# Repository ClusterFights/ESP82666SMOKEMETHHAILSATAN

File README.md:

ESP82666SMOKEMETHHAILSATAN

Imps are like clients. They're small and should only consume work units
Devils are like hosts. They parse the datasets and create work units

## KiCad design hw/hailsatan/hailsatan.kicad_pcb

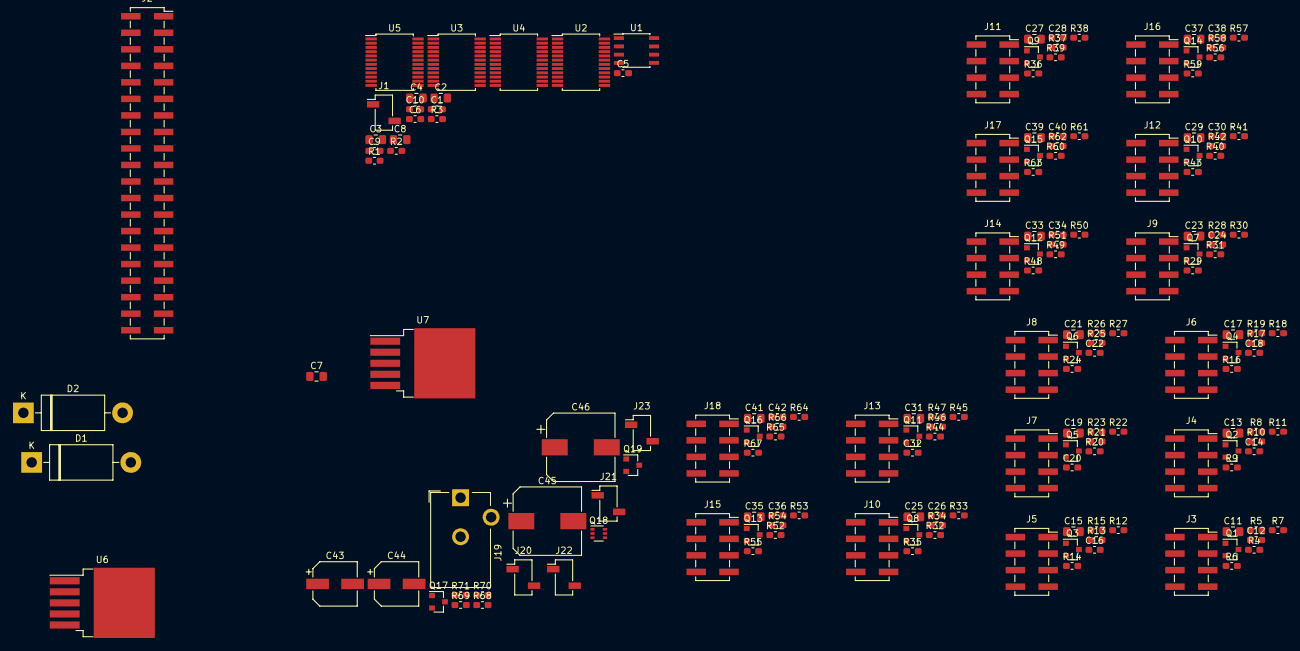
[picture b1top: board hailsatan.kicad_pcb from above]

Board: 2 copper layers, 168 parts (0 on the bottom side), 136 nets, no tracks yet.

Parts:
C1, C5, C6, C9, C10, C12, C14, C16, C18, C20, C22, C24, C26, C28, C30, C32, C34, C36, C38, C40, C42: 0.1uF; C_0603_1608Metric_Pad1.05x0.95mm_HandSolder
C2, C3, C4, C7, C8, C11, C13, C15, C17, C19, C21, C23, C25, C27, C29, C31, C33, C35, C37, C39, C41: 1uF; C_0805_2012Metric_Pad1.15x1.40mm_HandSolder
C43, C44: 100uF; CP_Elec_6.3x5.4_Nichicon
C45, C46: 1000uF; CP_Elec_10x10
D1, D2: 1N5822; D_DO-201AD_P15.24mm_Horizontal
J1, J20, J21, J22, J23: Conn_01x02; PinSocket_1x02_P2.54mm_Vertical_SMD_Pin1Left
J2: Raspberry_Pi_2_3; PinSocket_2x20_P2.54mm_Vertical_SMD
J3, J4, J5, J6, J7, J8, J9, J10, J11, J12, J13, J14, J15, J16, J17, J18: Conn_02x04_Odd_Even; PinSocket_2x04_P2.54mm_Vertical_SMD
J19: Barrel_Jack_Switch; BarrelJack_CUI_PJ-102AH_Horizontal
Q1, Q2, Q3, Q4, Q5, Q6, Q7, Q8, Q9, Q10, Q11, Q12, Q13, Q14, Q15, Q16, Q17: 2N7002; SOT-23
Q18: MMDT3906; SOT-363_SC-70-6
Q19: Si2319CDS; SOT-23
R1, R2, R3, R68, R69: 3.3k; R_0603_1608Metric_Pad1.05x0.95mm_HandSolder
R4, R5, R6, R7, R8, R9, R10, R11, R12, R13, R14, R15, R16, R17, R18, R19, R20, R21, R22, R23, R24, R25, R26, R27, R28, R29, R30, R31, R32, R33, R34, R35, R36, R37, R38, R39, R40, R41, R42, R43, R44, R45, R46, R47, R48, R49, R50, R51, R52, R53, R54, R55, R56, R57, R58, R59, R60, R61, R62, R63, R64, R65, R66, R67: 3.3K; R_0603_1608Metric_Pad1.05x0.95mm_HandSolder
R70: 10k; R_0603_1608Metric_Pad1.05x0.95mm_HandSolder
R71: 47k; R_0603_1608Metric_Pad1.05x0.95mm_HandSolder
U1: CAT24C256; SOIC-8_3.9x4.9mm_P1.27mm
U2, U3, U4, U5: CD74HC4067SM; SSOP-24_5.3x8.2mm_P0.65mm
U6: LM2576S-5; TO-263-5_TabPin3
U7: LM2576S-3.3; TO-263-5_TabPin3

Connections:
+3.3VA: C1.2, C2.2, J2.1, J2.17, R1.2, R2.2, R3.2, U1.8
+3V3: C3.2, C4.2, C5.2, C6.2, C7.2, C8.2, C9.2, C10.2, C11.1, C12.1, C13.1, C14.1, C15.1, C16.1, C17.1, C18.1, C19.1, C20.1, C21.1, C22.1, C23.1, C24.1, C25.1, C26.1, C27.1, C28.1, C29.1, C30.1, C31.1, C32.1, C33.1, C34.1, C35.1, C36.1, C37.1, C38.1, C39.1, C40.1, C41.1, C42.1, C46.1, J3.8, J4.8, J5.8, J6.8, J7.8, J8.8, J9.8, J10.8, J11.8, J12.8, J13.8, J14.8, J15.8, J16.8, J17.8, J18.8, J22.1, R4.1, R5.1, R6.1, R7.1, R8.1, R9.1, R10.1, R11.1, R12.1, R13.1, R14.1, R15.1, R16.1, R17.1, R18.1, R19.1, R20.1, R21.1, R22.1, R23.1, R24.1, R25.1, R26.1, R27.1, R28.1, R29.1, R30.1, R31.1, R32.1, R33.1, R34.1, R35.1, R36.1, R37.1, R38.1, R39.1, R40.1, R41.1, R42.1, R43.1, R44.1, R45.1, R46.1, R47.1, R48.1, R49.1, R50.1, R51.1, R52.1, R53.1, R54.1, R55.1, R56.1, R57.1, R58.1, R59.1, R60.1, R61.1, R62.1, R63.1, R64.1, R65.1, R66.1, R67.1, U2.24, U3.24, U4.24, U5.24, U7.4
+5V: C45.1, J21.1, Q18.1, Q19.3, U6.4
+5VA: J2.2, J2.4, J23.1, Q18.4, Q19.2
/ESP-01_00/CH_PD: J3.4, R6.2
/ESP-01_00/GPIO0: J3.7, Q1.3, R4.2
/ESP-01_00/GPIO2: J3.3, R5.2
/ESP-01_01/CH_PD: J7.4, R22.2
/ESP-01_01/GPIO0: J7.7, Q5.3, R20.2
/ESP-01_01/GPIO2: J7.3, R21.2
/ESP-01_02/CH_PD: J9.4, R30.2
/ESP-01_02/GPIO0: J9.7, Q7.3, R28.2
/ESP-01_02/GPIO2: J9.3, R29.2
/ESP-01_03/CH_PD: J6.4, R18.2
/ESP-01_03/GPIO0: J6.7, Q4.3, R16.2
/ESP-01_03/GPIO2: J6.3, R17.2
/ESP-01_04/CH_PD: J8.4, R26.2
/ESP-01_04/GPIO0: J8.7, Q6.3, R24.2
/ESP-01_04/GPIO2: J8.3, R25.2
/ESP-01_05/CH_PD: J11.4, R38.2
/ESP-01_05/GPIO0: J11.7, Q9.3, R36.2
/ESP-01_05/GPIO2: J11.3, R37.2
/ESP-01_06/CH_PD: J12.4, R42.2
/ESP-01_06/GPIO0: J12.7, Q10.3, R40.2
/ESP-01_06/GPIO2: J12.3, R41.2
/ESP-01_07/CH_PD: J10.4, R34.2
/ESP-01_07/GPIO0: J10.7, Q8.3, R32.2
/ESP-01_07/GPIO2: J10.3, R33.2
/ESP-01_08/CH_PD: J13.4, R46.2
/ESP-01_08/GPIO0: J13.7, Q11.3, R44.2
/ESP-01_08/GPIO2: J13.3, R45.2
/ESP-01_09/CH_PD: J14.4, R50.2
/ESP-01_09/GPIO0: J14.7, Q12.3, R48.2
/ESP-01_09/GPIO2: J14.3, R49.2
/ESP-01_10/CH_PD: J15.4, R54.2
/ESP-01_10/GPIO0: J15.7, Q13.3, R52.2
/ESP-01_10/GPIO2: J15.3, R53.2
/ESP-01_11/CH_PD: J16.4, R58.2
/ESP-01_11/GPIO0: J16.7, Q14.3, R56.2
/ESP-01_11/GPIO2: J16.3, R57.2
/ESP-01_12/CH_PD: J17.4, R62.2
/ESP-01_12/GPIO0: J17.7, Q15.3, R60.2
/ESP-01_12/GPIO2: J17.3, R61.2
/ESP-01_13/CH_PD: J18.4, R66.2
/ESP-01_13/GPIO0: J18.7, Q16.3, R64.2
/ESP-01_13/GPIO2: J18.3, R65.2
/ESP-01_14/CH_PD: J4.4, R10.2
/ESP-01_14/GPIO0: J4.7, Q2.3, R8.2
/ESP-01_14/GPIO2: J4.3, R9.2
/ESP-01_15/CH_PD: J5.4, R14.2
/ESP-01_15/GPIO0: J5.7, Q3.3, R12.2
/ESP-01_15/GPIO2: J5.3, R13.2
/ESP_BOOT_0: Q1.1, U4.9
/ESP_BOOT_1: Q5.1, U4.8
/ESP_BOOT_2: Q7.1, U4.7
/ESP_BOOT_3: Q4.1, U4.6
/ESP_BOOT_4: Q6.1, U4.5
/ESP_BOOT_5: Q9.1, U4.4
/ESP_BOOT_6: Q10.1, U4.3
/ESP_BOOT_7: Q8.1, U4.2
/ESP_BOOT_8: Q11.1, U4.23
/ESP_BOOT_9: Q12.1, U4.22
/ESP_BOOT_10: Q13.1, U4.21
/ESP_BOOT_11: Q14.1, U4.20
/ESP_BOOT_12: Q15.1, U4.19
/ESP_BOOT_13: Q16.1, U4.18
/ESP_BOOT_14: Q2.1, U4.17
/ESP_BOOT_15: Q3.1, U4.16
/ESP_BOOT_ALL: J2.36, U4.1
/ESP_RST_0: J3.6, R7.2, U3.9
/ESP_RST_1: J7.6, R23.2, U3.8
/ESP_RST_2: J9.6, R31.2, U3.7
/ESP_RST_3: J6.6, R19.2, U3.6
/ESP_RST_4: J8.6, R27.2, U3.5
/ESP_RST_5: J11.6, R39.2, U3.4
/ESP_RST_6: J12.6, R43.2, U3.3
/ESP_RST_7: J10.6, R35.2, U3.2
/ESP_RST_8: J13.6, R47.2, U3.23
/ESP_RST_9: J14.6, R51.2, U3.22
/ESP_RST_10: J15.6, R55.2, U3.21
/ESP_RST_11: J16.6, R59.2, U3.20
/ESP_RST_12: J17.6, R63.2, U3.19
/ESP_RST_13: J18.6, R67.2, U3.18
/ESP_RST_14: J4.6, R11.2, U3.17
/ESP_RST_15: J5.6, R15.2, U3.16
/ESP_RST_ALL: J2.11, U3.1
/ESP_RX_0: J3.5, U2.9
/ESP_RX_1: J7.5, U2.8
/ESP_RX_2: J9.5, U2.7
/ESP_RX_3: J6.5, U2.6
/ESP_RX_4: J8.5, U2.5
/ESP_RX_5: J11.5, U2.4
/ESP_RX_6: J12.5, U2.3
/ESP_RX_7: J10.5, U2.2
/ESP_RX_8: J13.5, U2.23
/ESP_RX_9: J14.5, U2.22
/ESP_RX_10: J15.5, U2.21
/ESP_RX_11: J16.5, U2.20
/ESP_RX_12: J17.5, U2.19
/ESP_RX_13: J18.5, U2.18
/ESP_RX_14: J4.5, U2.17
/ESP_RX_15: J5.5, U2.16
/ESP_RX_ALL: J2.10, U2.1
/ESP_TX_0: J3.2, U5.9
/ESP_TX_1: J7.2, U5.8
/ESP_TX_2: J9.2, U5.7
/ESP_TX_3: J6.2, U5.6
/ESP_TX_4: J8.2, U5.5
/ESP_TX_5: J11.2, U5.4
/ESP_TX_6: J12.2, U5.3
/ESP_TX_7: J10.2, U5.2
/ESP_TX_8: J13.2, U5.23
/ESP_TX_9: J14.2, U5.22
/ESP_TX_10: J15.2, U5.21
/ESP_TX_11: J16.2, U5.20
/ESP_TX_12: J17.2, U5.19
/ESP_TX_13: J18.2, U5.18
/ESP_TX_14: J4.2, U5.17
/ESP_TX_15: J5.2, U5.16
/ESP_TX_ALL: J2.8, U5.1
/ID_SC: J2.28, R3.1, U1.6
/ID_SD: J2.27, R2.1, U1.5
/MUX_SEL_0: J2.15, U2.10, U3.10, U4.10, U5.10
/MUX_SEL_1: J2.16, U2.11, U3.11, U4.11, U5.11
/MUX_SEL_2: J2.18, U2.14, U3.14, U4.14, U5.14
/MUX_SEL_3: J2.22, U2.13, U3.13, U4.13, U5.13
/~3.3V_EN~: J2.13, Q17.1, R68.2
/~MUX_EN~: J2.37, U2.15, U3.15, U4.15, U5.15
GND: C1.1, C2.1, C3.1, C4.1, C5.1, C6.1, C7.1, C8.1, C9.1, C10.1, C11.2, C12.2, C13.2, C14.2, C15.2, C16.2, C17.2, C18.2, C19.2, C20.2, C21.2, C22.2, C23.2, C24.2, C25.2, C26.2, C27.2, C28.2, C29.2, C30.2, C31.2, C32.2, C33.2, C34.2, C35.2, C36.2, C37.2, C38.2, C39.2, C40.2, C41.2, C42.2, C43.2, C44.2, C45.2, C46.2, D1.2, D2.2, J1.2, J2.6, J2.9, J2.14, J2.20, J2.25, J2.30, J2.34, J2.39, J3.1, J4.1, J5.1, J6.1, J7.1, J8.1, J9.1, J10.1, J11.1, J12.1, J13.1, J14.1, J15.1, J16.1, J17.1, J18.1, J19.2, J19.3, J20.2, J21.2, J22.2, J23.2, Q1.2, Q2.2, Q3.2, Q4.2, Q5.2, Q6.2, Q7.2, Q8.2, Q9.2, Q10.2, Q11.2, Q12.2, Q13.2, Q14.2, Q15.2, Q16.2, Q17.2, R68.1, R70.1, R71.1, U1.1, U1.2, U1.3, U1.4, U2.12, U3.12, U4.12, U5.12, U6.3, U6.5, U7.3
unnamed: D1.1, U6.2
unnamed: D2.1, U7.2
unnamed: J1.1, R1.1, U1.7
unnamed: Q17.3, R69.1, U7.5
unnamed: Q18.2, Q18.5, Q18.6, R70.2
unnamed: Q18.3, Q19.1, R71.2
VDD: C43.1, C44.1, J19.1, J20.1, R69.2, U6.1, U7.1

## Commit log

2019-04-17 first commit. test can list directories and the makefile can build and run the program
2019-04-17 test.c now parse argument to specific directory
2019-04-17 custom directory definition for default dir if none are provided in arguments
2019-04-17 began implementing stat.h to check if file or directory. not done yet
2019-04-20 added esp32 project template
2019-04-20 added mqtt example projects
2019-04-23 added older hw files
2019-04-23 removed unnecessary sdk tools, reorganized fs
2019-04-24 removed build folder, added gitignore, added rpi toolchains
